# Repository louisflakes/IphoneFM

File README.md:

# IphoneFM

A MagSafe accessory for the iPhone 17 Pro that transmits and receives FM (88–108 MHz).
The board lies flat on the back of the phone and connects to the phone through a very short, flexible USB-C cable.
The iPhone sees a USB audio device: it sends audio to transmit, or plays audio the board receives.
Transmit and receive are half duplex, selected by a TX/RX slider. Three thumbwheels set the frequency; a DIP switch sets the transmit level.

The project also asks a question: can Claude design a working PCB, from requirements to a board JLCPCB assembles in full?

## Status

**Rev A** is the active design: the analog-FM rendition, option D2. The MCU computes the FM modulation and streams it over I²S to a TI LMX2571 synthesizer, whose internal VCO is the carrier ([modulation-strategies.md](design/rev-a/modulation-strategies.md)). Every part is checked against its datasheet, every pin is mapped to a net, and the placement is agreed. Next: the KiCad build, following [kicad-build-procedure.md](design/rev-a/kicad-build-procedure.md) one step at a time.

| Design | Transmitter | Status |
|---|---|---|
| Rev A (analog FM, D2) | TI LMX2571, direct digital FM | **Active** |
| Plan C | onsemi LV2285VB | Archived: the transmitter is obsolete and needs a large minimum order |
| Plans A, B | | Archived |

## Rev A design files (`design/rev-a/`)

| File | What it is |
|---|---|
| [netlist.json](design/rev-a/netlist.json) | **Source of truth:** every part (designator, part number, JLC code, package) and every pin with its net |
| [bom.md](design/rev-a/bom.md) | Why each part and value was chosen, chain by chain, with datasheet pages |
| [wiring.html](design/rev-a/wiring.html) | Wiring diagram and netlist table |
| [layout.html](design/rev-a/layout.html) | True-size parts on the board envelope, and the Rev A placement |
| [placement-rules.md](design/rev-a/placement-rules.md) | Placement rules, with the user's feedback |
| [sourcing.md](design/rev-a/sourcing.md) | Key parts, JLC stock and second routes |
| [modulation-strategies.md](design/rev-a/modulation-strategies.md) | Why direct digital FM on the LMX2571 |
| [verification.md](design/rev-a/verification.md) | The checks that keep every file, and later KiCad, in step |
| [kicad-build-procedure.md](design/rev-a/kicad-build-procedure.md) | The KiCad build, one reviewed step at a time |

The KiCad project goes in `kicad/rev-a/`. Open the `.html` pages in a browser; `layout.html` needs `local/apple/phone-outline.js`, which stays on the design PC (Apple's drawings say not to republish it).

## Checks

```
python tools/netcheck.py                      # netlist.json against itself, bom.md and wiring.html
python tools/kicadcheck.py --net … --pcb …    # KiCad's exports against netlist.json and the Rev A placement
python tools/kicadcheck_test.py               # proves kicadcheck catches real faults
```

## Open items

1. KiCad build: [kicad-build-procedure.md](design/rev-a/kicad-build-procedure.md).
2. Before ordering: re-run JLC stock for the thin parts (Si4705, LMX2571) and the two global-sourcing parts (STM32U535, TDP06 DIP).
3. Bench checks on the first boards: which slider direction is TX (TP4); the SMA's centre contact; transmit level and harmonics in the Faraday cage against FCC §15.239 as a target; the receiver's matching inductor L1 by RSSI sweep (AN383 p50–53); 3V3 current.
4. Firmware: UAC2 audio, FM stereo multiplex and pre-emphasis, the I²S deviation stream to the LMX2571, receiver control over I²C, wheels, DIP-aware power setting, LED.
5. MagSafe enclosure (user-owned), with slots for the wheels, slider, DIP levers and USB-C, and a light pipe for the LED.

## Repository layout

| Path | Contents |
|---|---|
| `design/rev-a/` | The active design (above) |
| `kicad/rev-a/` | The KiCad project |
| `design/archive/` | Plans A, B and C, no longer developed |
| `docs/decisions.md` | Design decisions and their sources |
| `docs/pcb-design-workflow.md` | PCB capture and layout workflow and rules, cited to reference books, with conflicts flagged |
| `docs/reference-designs.md` | Existing FM transmitter designs, for patterns only |
| `docs/datasheets/` | Every datasheet and spec the design was checked against, with an index |
| `tools/` | Design checks, DigiKey/JLC stock scripts, KiCad setup |
| `.mcp.json` | KiCad MCP server for Claude Code |
| `Imported/` | Notes from an earlier session, kept for later reference |

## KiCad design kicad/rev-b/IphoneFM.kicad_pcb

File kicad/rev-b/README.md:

KiCad project for IphoneFM Rev B: Rev A (tag rev-a-reviewed) with the new front panel. Built from ../../design/rev-b/build-procedure.md; checked with ../../tools/kicadcheck.py (IPHONEFM_REV=rev-b).

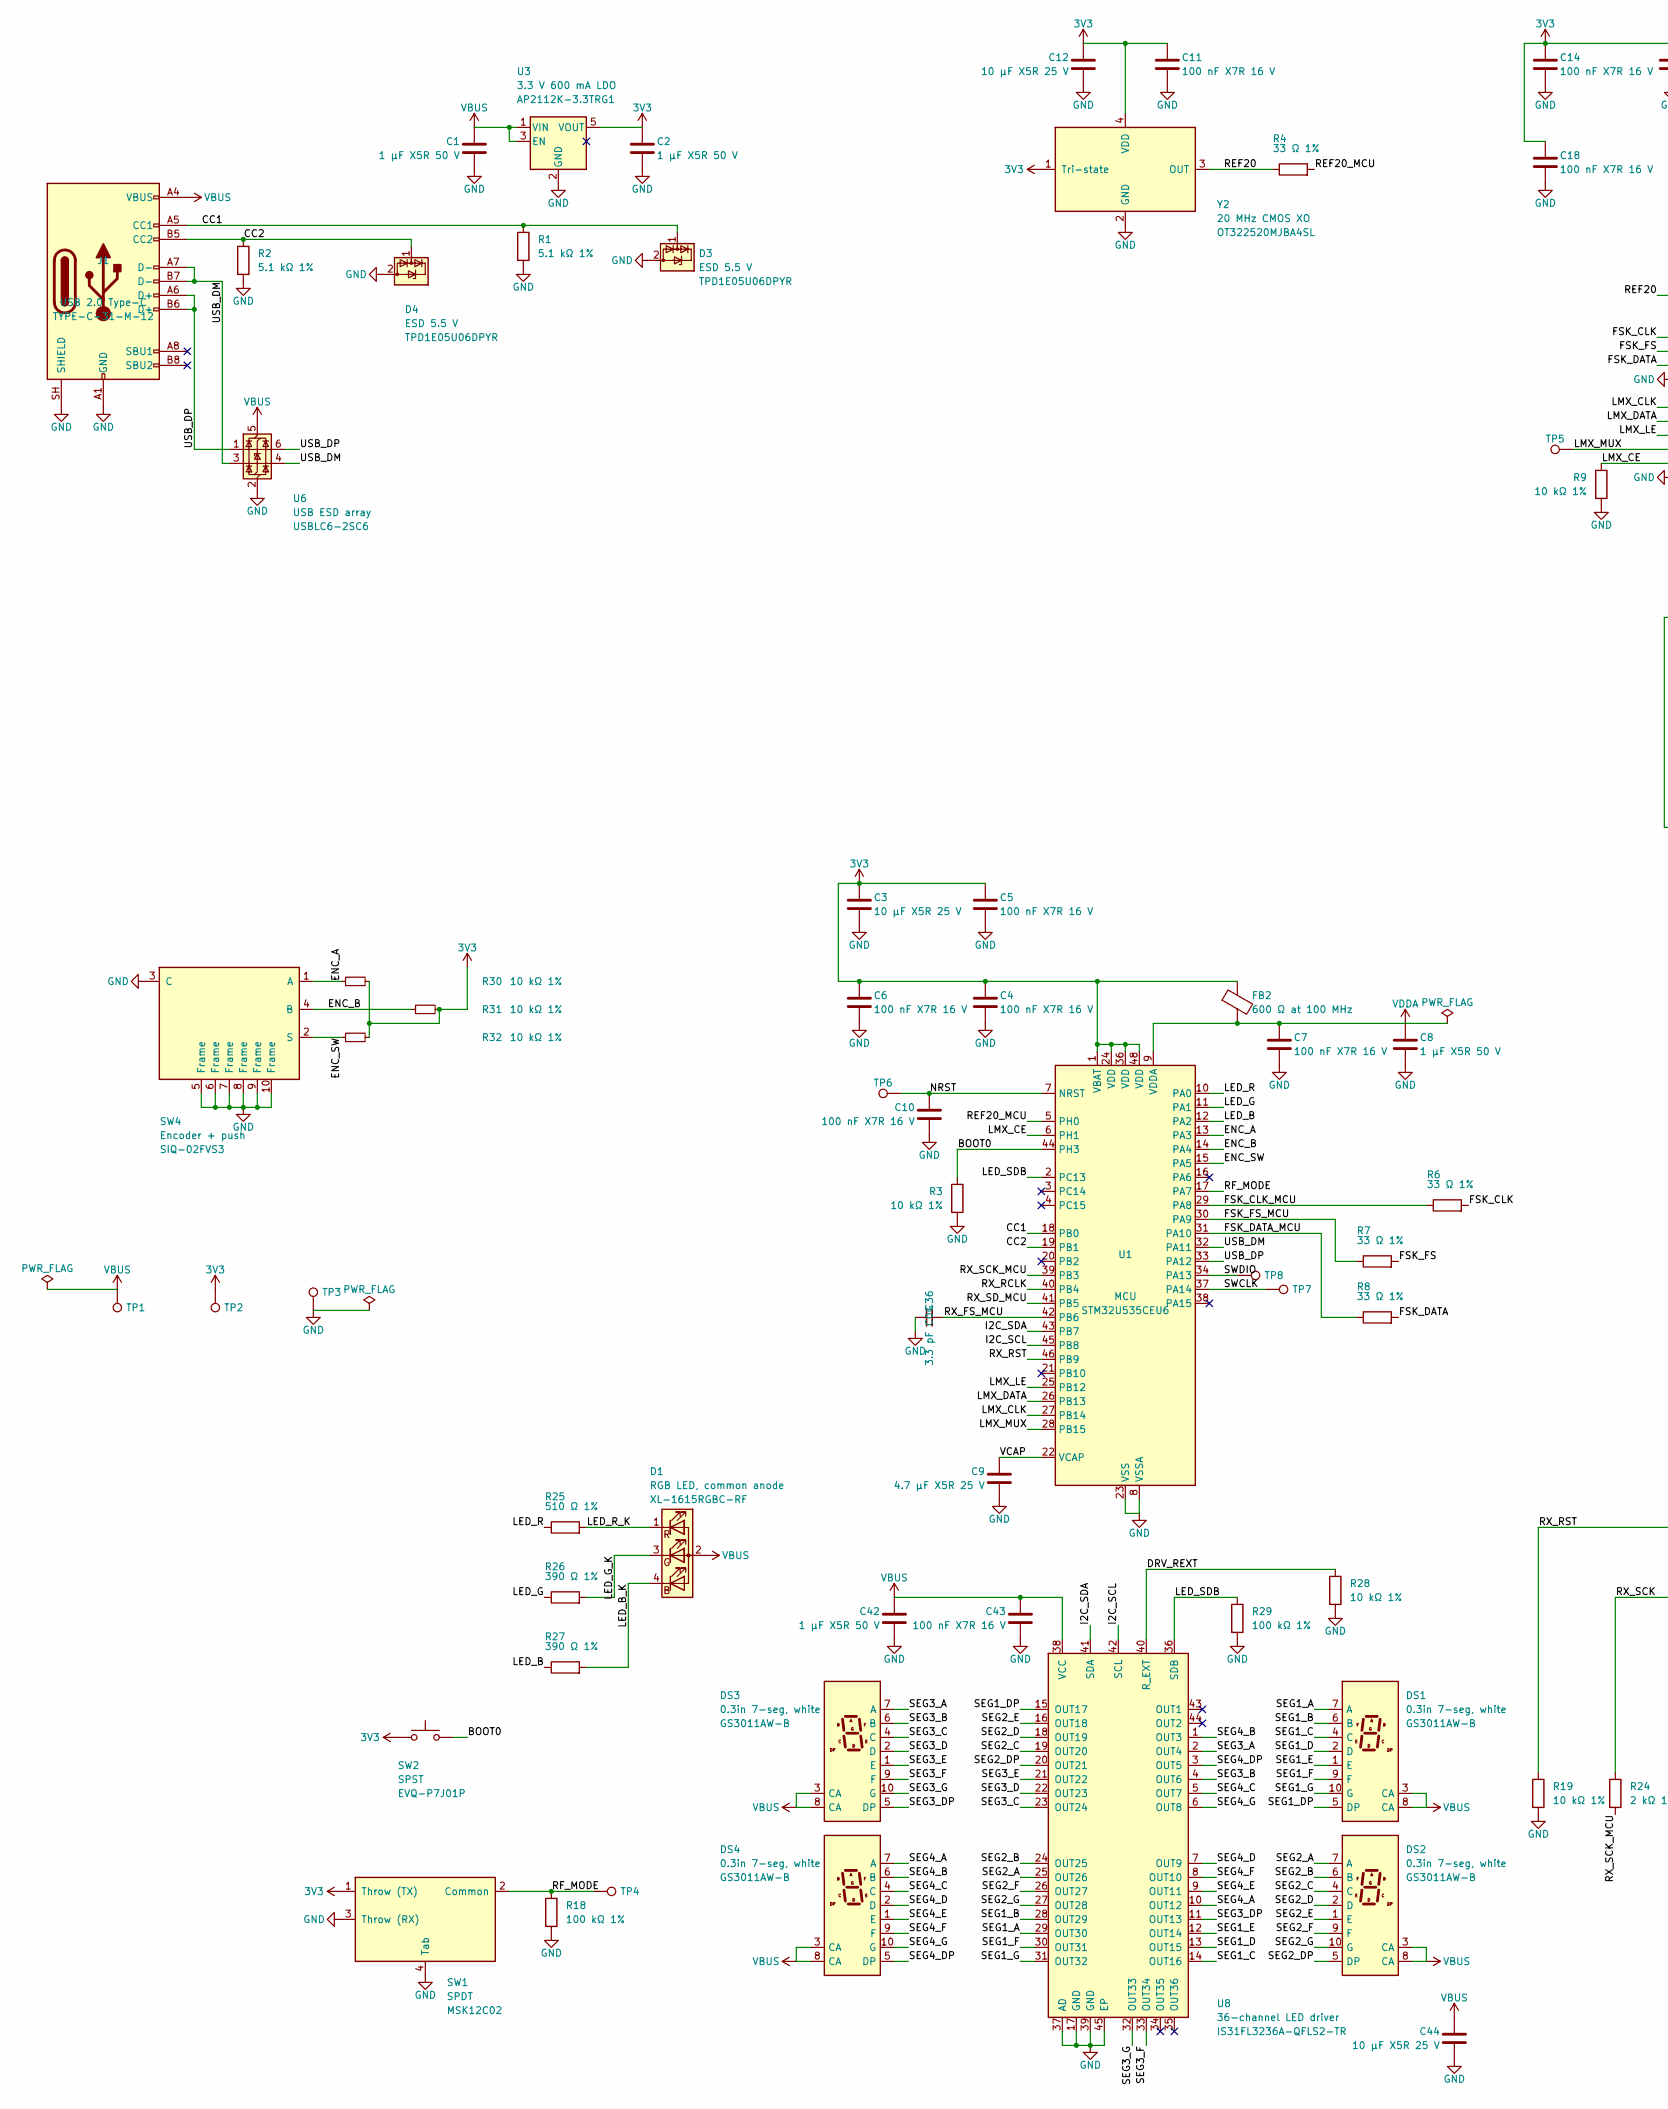
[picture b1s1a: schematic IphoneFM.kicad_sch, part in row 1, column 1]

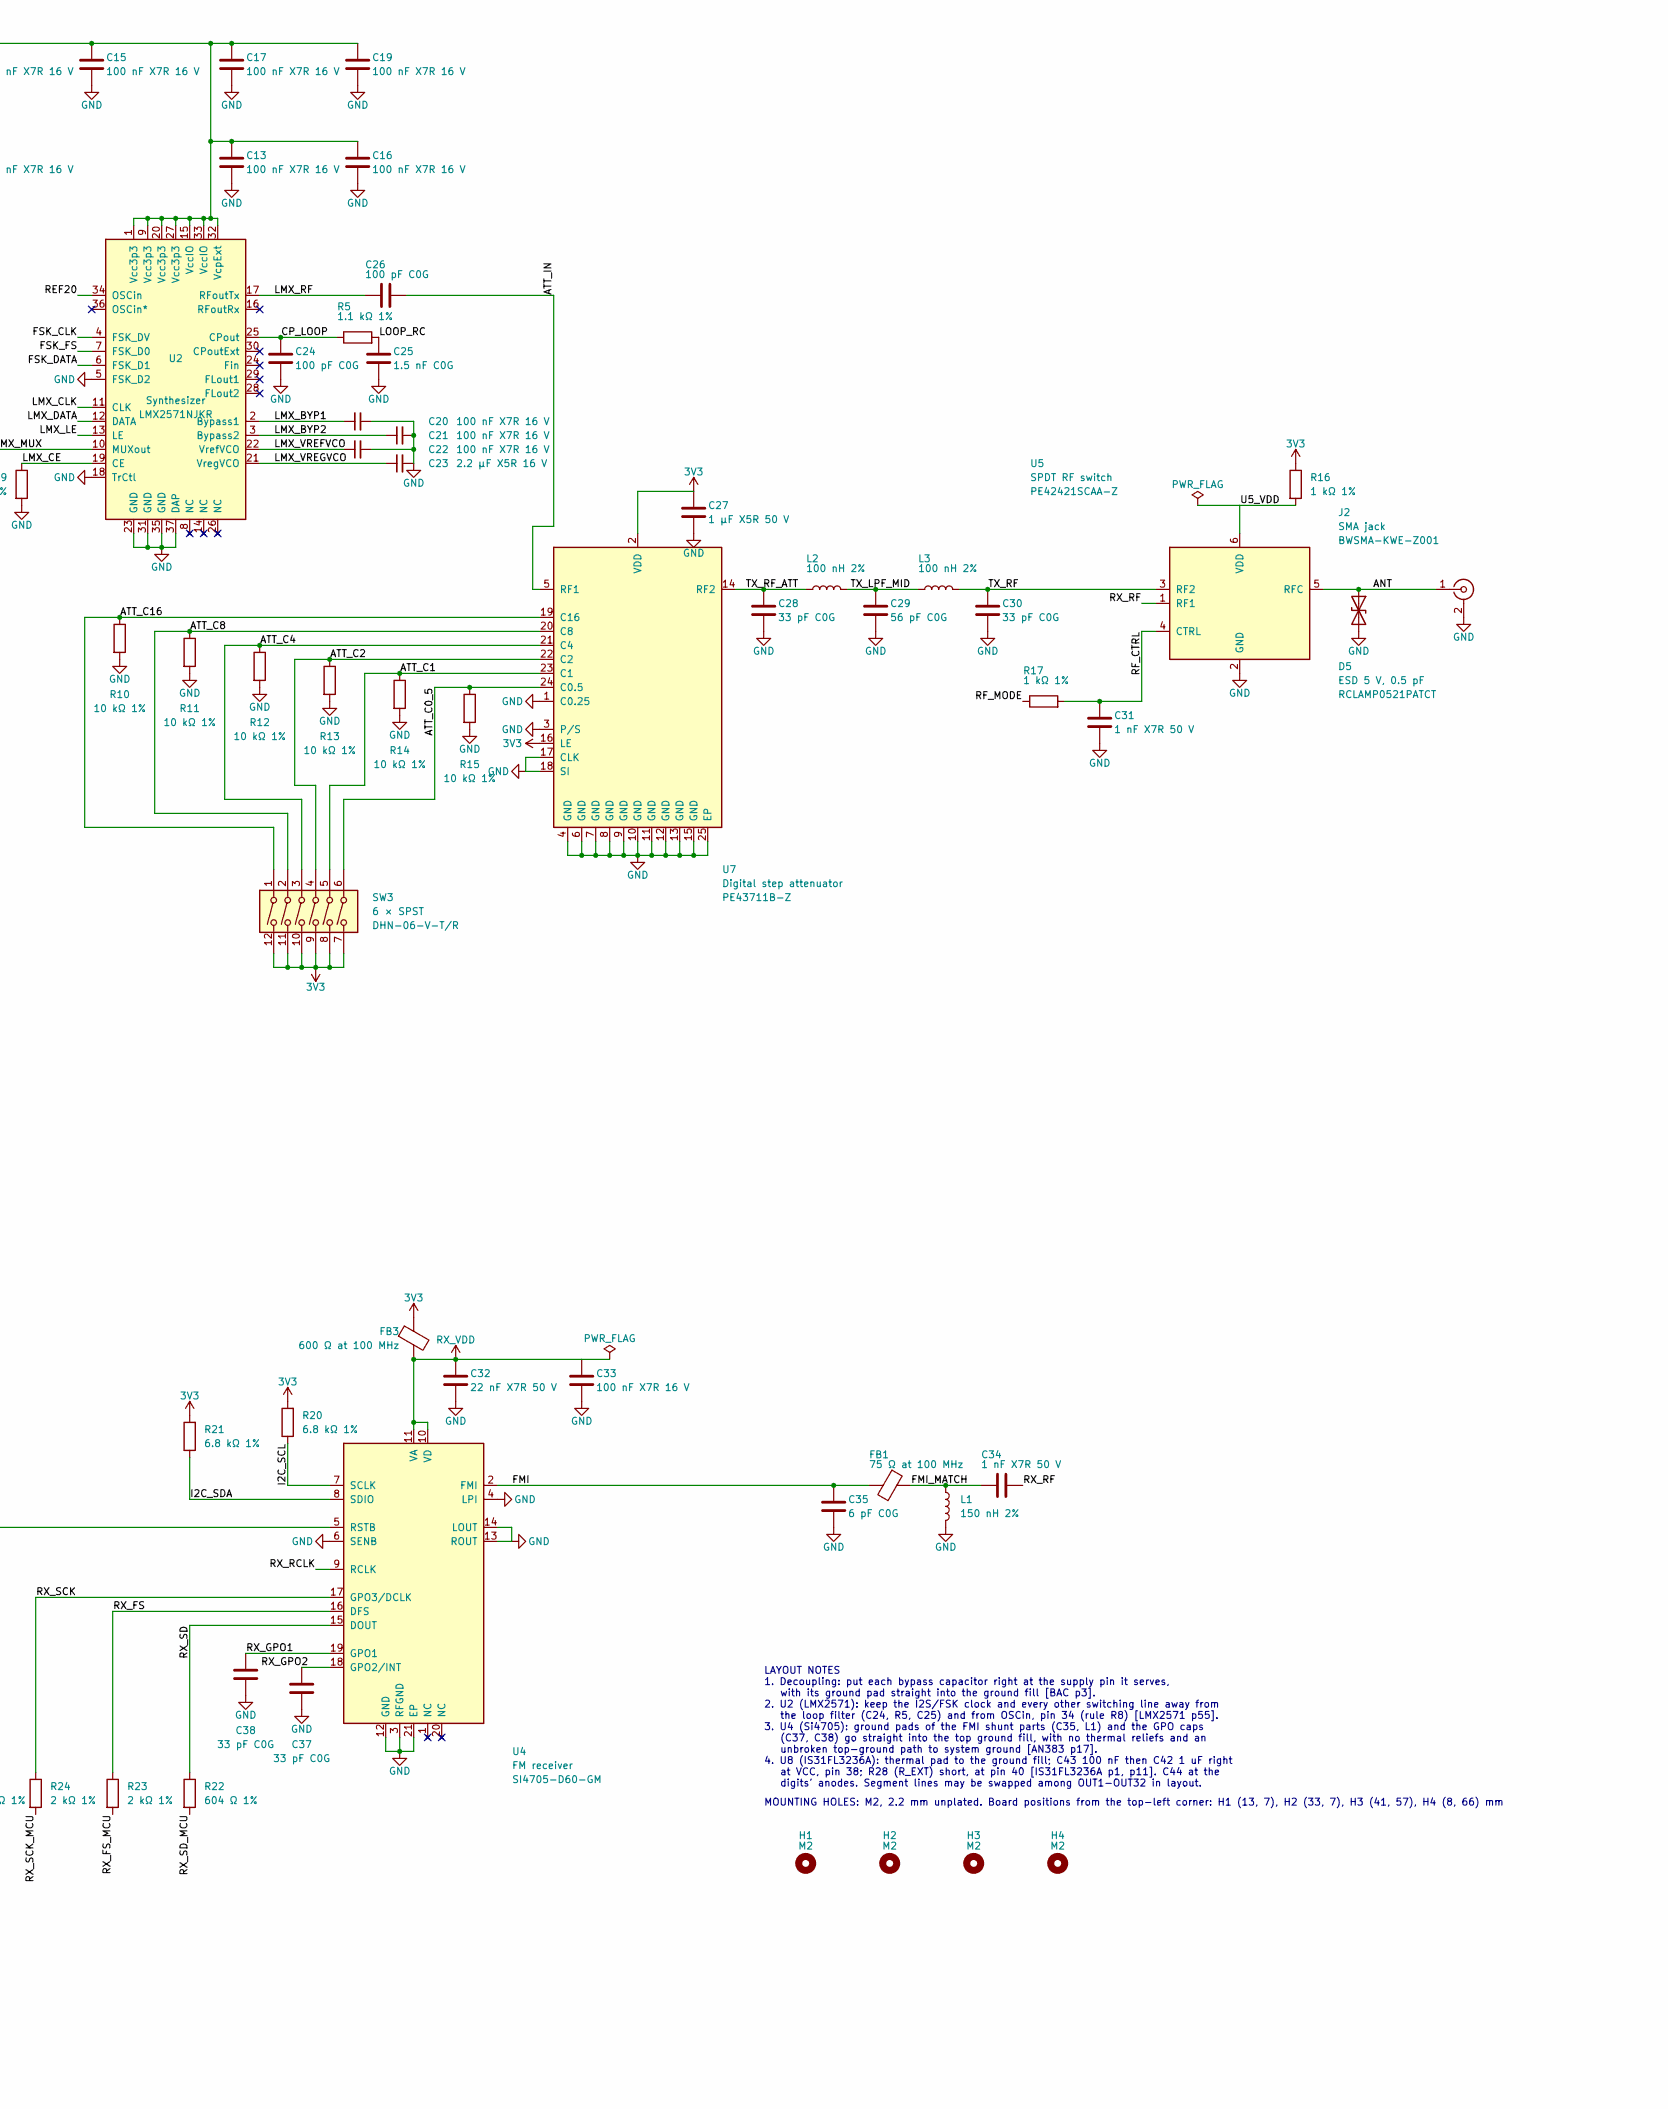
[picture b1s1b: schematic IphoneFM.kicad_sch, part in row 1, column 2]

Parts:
C1, C2, C8, C27, C42: 1 µF X5R 50 V; C_0603_1608Metric; MPN CL10A105KB8NNNC; LCSC C15849
C3, C12, C44: 10 µF X5R 25 V; C_0805_2012Metric; MPN CL21A106KAYNNNE; LCSC C15850
C4, C5, C6, C7, C10, C11, C13, C14, C15, C16, C17, C18, C19, C20, C21, C22, C33, C43: 100 nF X7R 16 V; C_0402_1005Metric; MPN CL05B104KO5NNNC; LCSC C1525
C9: 4.7 µF X5R 25 V; C_0805_2012Metric; MPN CL21A475KAQNNNE; LCSC C1779
C23: 2.2 µF X5R 16 V; C_0603_1608Metric; MPN CL10A225KO8NNNC; LCSC C23630
C24, C26: 100 pF C0G; C_0402_1005Metric; MPN 0402CG101J500NT; LCSC C1546
C25: 1.5 nF C0G; C_0402_1005Metric; MPN GRM1555C1H152JA01D; LCSC C668348
C28, C30, C37, C38: 33 pF C0G; C_0402_1005Metric; MPN 0402CG330J500NT; LCSC C1562
C29: 56 pF C0G; C_0402_1005Metric; MPN CC0402JRNPO9BN560; LCSC C107007
C31, C34: 1 nF X7R 50 V; C_0402_1005Metric; MPN 0402B102K500NT; LCSC C1523
C32: 22 nF X7R 50 V; C_0402_1005Metric; MPN 0402B223K500NT; LCSC C1532
C35: 6 pF C0G; C_0402_1005Metric; MPN GJM1555C1H6R0CB01D; LCSC C161330
C36: 3.3 pF C0G; C_0402_1005Metric; MPN GRM1555C1H3R3CA01D; LCSC C76968
D1: RGB LED, common anode; LED_RGB_XINGLIGHT_XL-1615RGBC_1.6x1.5mm; MPN XL-1615RGBC-RF; LCSC C965840
D3, D4: ESD 5.5 V; Texas_DPY0002A_0.6x1mm_P0.65mm; MPN TPD1E05U06DPYR; LCSC C436349
D5: ESD 5 V, 0.5 pF; D_SOD-882; MPN RCLAMP0521PATCT; LCSC C117554
DS1, DS2, DS3, DS4: 0.3in 7-seg, white; LED_7Segment_Guangcai_GS3011_7.3x12mm_P1.5mm; MPN GS3011AW-B; LCSC C22462661
FB1: 75 Ω at 100 MHz; L_0402_1005Metric; MPN BLM15GA750SN1D; LCSC C113009
FB2, FB3: 600 Ω at 100 MHz; L_0402_1005Metric; MPN BLM15AG601SN1D; LCSC C76884
H1, H2, H3, H4: M2; MountingHole_2.2mm_M2
J1: USB 2.0 Type-C; USB_C_Receptacle_HRO_TYPE-C-31-M-12_2020; MPN TYPE-C-31-M-12; LCSC C165948
J2: SMA jack; SMA_BAT_Wireless_BWSMA-KWE-Z001; MPN BWSMA-KWE-Z001; LCSC C496551
L1: 150 nH 2%; L_0603_1608Metric; MPN LQW18ANR15G00D; LCSC C113131
L2, L3: 100 nH 2%; L_0603_1608Metric; MPN LQW18ANR10G00D; LCSC C98088
R1, R2: 5.1 kΩ 1%; R_0402_1005Metric; MPN 0402WGF5101TCE; LCSC C25905
R3, R9, R10, R11, R12, R13, R14, R15, R19, R28, R30, R31, R32: 10 kΩ 1%; R_0402_1005Metric; MPN 0402WGF1002TCE; LCSC C25744
R4, R6, R7, R8: 33 Ω 1%; R_0402_1005Metric; MPN 0402WGF330JTCE; LCSC C25105
R5: 1.1 kΩ 1%; R_0402_1005Metric; MPN ERJ-2RKF1101X; LCSC C409028
R16, R17: 1 kΩ 1%; R_0402_1005Metric; MPN 0402WGF1001TCE; LCSC C11702
R18, R29: 100 kΩ 1%; R_0402_1005Metric; MPN 0402WGF1003TCE; LCSC C25741
R20, R21: 6.8 kΩ 1%; R_0402_1005Metric; MPN RC0402FR-076K8L; LCSC C93940
R22: 604 Ω 1%; R_0402_1005Metric; MPN RC0402FR-07604RL; LCSC C273693
R23, R24: 2 kΩ 1%; R_0402_1005Metric; MPN 0402WGF2001TCE; LCSC C4109
R25: 510 Ω 1%; R_0402_1005Metric; MPN 0402WGF5100TCE; LCSC C25123
R26, R27: 390 Ω 1%; R_0402_1005Metric; MPN RC0402FR-07390RL; LCSC C137997
SW1: SPDT; SW_SPDT_Shouhan_MSK12C02_Tabs4; MPN MSK12C02; LCSC C431540
SW2: SPST; SW_SPST_EVQP7A; MPN EVQ-P7J01P; LCSC C2828254
SW3: 6 × SPST; SW_DIP_SPSTx06_Slide_Diptronics_DHN-06_W6.15mm_P1.27mm; MPN DHN-06-V-T/R; LCSC C224997
SW4: Encoder + push; RotaryEncoder_Switch_Mitsumi_SIQ-02FVS3; MPN SIQ-02FVS3; LCSC C2925423
TP1: VBUS; TestPoint_Pad_D1.5mm
TP2: 3V3; TestPoint_Pad_D1.5mm
TP3: GND; TestPoint_Pad_D1.5mm
TP4: RF_MODE; TestPoint_Pad_D1.5mm
TP5: LMX_MUX; TestPoint_Pad_D1.5mm
TP6: NRST; TestPoint_Pad_D1.5mm
TP7: SWCLK; TestPoint_Pad_D1.5mm
TP8: SWDIO; TestPoint_Pad_D1.5mm
U1: MCU; QFN-48-1EP_7x7mm_P0.5mm_EP5.6x5.6mm; MPN STM32U535CEU6; LCSC C22454224
U2: Synthesizer; TI_NJK0036A_WQFN-36-1EP_6x6mm_P0.5mm_EP4.6x4.6mm; MPN LMX2571NJKR; LCSC C440388
U3: 3.3 V 600 mA LDO; SOT-23-5; MPN AP2112K-3.3TRG1; LCSC C51118
U4: FM receiver; SiliconLabs_QFN-20-1EP_3x3mm_P0.5mm_EP1.8x1.8mm; MPN SI4705-D60-GM; LCSC C1526114
U5: SPDT RF switch; SOT-363_SC-70-6; MPN PE42421SCAA-Z; LCSC C470893
U6: USB ESD array; SOT-23-6; MPN USBLC6-2SC6; LCSC C7519
U7: Digital step attenuator; QFN-24-1EP_4x4mm_P0.5mm_EP2.75x2.75mm; MPN PE43711B-Z; LCSC C470929
U8: 36-channel LED driver; Lumissil_QFN-44-1EP_5x5mm_P0.4mm_EP2.45x2.45mm; MPN IS31FL3236A-QFLS2-TR; LCSC C246443
Y2: 20 MHz CMOS XO; Oscillator_SMD_SiT_PQFN-4Pin_3.2x2.5mm; MPN OT322520MJBA4SL; LCSC C725987

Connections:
3V3: C2.1, C3.1, C4.1, C5.1, C6.1, C11.1, C12.1, C13.1, C14.1, C15.1, C16.1, C17.1, C18.1, C19.1, C27.1, FB2.1, FB3.1, R16.1, R20.2, R21.2, R30.2, R31.2, R32.2, SW1.1 (Throw_(TX)), SW2.1, SW3.7, SW3.8, SW3.9, SW3.10, SW3.11, SW3.12, TP2.1 (1_1), U1.1 (VBAT), U1.24 (VDD), U1.36 (VDD), U1.48 (VDD), U2.1 (Vcc3p3), U2.9 (Vcc3p3), U2.15 (VccIO), U2.20 (Vcc3p3), U2.27 (Vcc3p3), U2.32 (VcpExt), U2.33 (VccIO), U3.5 (VOUT), U7.2 (VDD), U7.16 (LE), Y2.1 (Tri-state), Y2.4 (VDD)
/ANT: D5.1 (A1), J2.1 (In), U5.5 (RFC)
/ATT_C0_5: R15.1, SW3.6, U7.24 (C0.5)
/ATT_C1: R14.1, SW3.5, U7.23 (C1)
/ATT_C2: R13.1, SW3.4, U7.22 (C2)
/ATT_C4: R12.1, SW3.3, U7.21 (C4)
/ATT_C8: R11.1, SW3.2, U7.20 (C8)
/ATT_C16: R10.1, SW3.1, U7.19 (C16)
/ATT_IN: C26.2, U7.5 (RF1)
/BOOT0: R3.1, SW2.2, U1.44 (PH3)
/CC1: D3.1 (I/O), J1.A5 (CC1), R1.1, U1.18 (PB0)
/CC2: D4.1 (I/O), J1.B5 (CC2), R2.1, U1.19 (PB1)
/CP_LOOP: C24.1, R5.1, U2.25 (CPout)
/DRV_REXT: R28.1, U8.40 (R_EXT)
/ENC_A: R30.1, SW4.1 (A), U1.13 (PA3)
/ENC_B: R31.1, SW4.4 (B), U1.14 (PA4)
/ENC_SW: R32.1, SW4.2 (S), U1.15 (PA5)
/FMI: C35.1, FB1.2, U4.2 (FMI)
/FMI_MATCH: C34.2, FB1.1, L1.1
/FSK_CLK: R6.2, U2.4 (FSK_DV)
/FSK_CLK_MCU: R6.1, U1.29 (PA8)
/FSK_DATA: R8.2, U2.6 (FSK_D1)
/FSK_DATA_MCU: R8.1, U1.31 (PA10)
/FSK_FS: R7.2, U2.7 (FSK_D0)
/FSK_FS_MCU: R7.1, U1.30 (PA9)
/I2C_SCL: R20.1, U1.45 (PB8), U4.7 (SCLK), U8.42 (SCL)
/I2C_SDA: R21.1, U1.43 (PB7), U4.8 (SDIO), U8.41 (SDA)
/LED_B: R27.1, U1.12 (PA2)
/LED_B_K: D1.4 (BK), R27.2
/LED_G: R26.1, U1.11 (PA1)
/LED_G_K: D1.3 (GK), R26.2
/LED_R: R25.1, U1.10 (PA0)
/LED_R_K: D1.1 (RK), R25.2
/LED_SDB: R29.1, U1.2 (PC13), U8.36 (SDB)
/LMX_BYP1: C20.1, U2.2 (Bypass1)
/LMX_BYP2: C21.1, U2.3 (Bypass2)
/LMX_CE: R9.1, U1.6 (PH1), U2.19 (CE)
/LMX_CLK: U1.27 (PB14), U2.11 (CLK)
/LMX_DATA: U1.26 (PB13), U2.12 (DATA)
/LMX_LE: U1.25 (PB12), U2.13 (LE)
/LMX_MUX: TP5.1 (1_1), U1.28 (PB15), U2.10 (MUXout)
/LMX_RF: C26.1, U2.17 (RFoutTx)
/LMX_VREFVCO: C22.1, U2.22 (VrefVCO)
/LMX_VREGVCO: C23.1, U2.21 (VregVCO)
/LOOP_RC: C25.1, R5.2
/NRST: C10.1, TP6.1 (1_1), U1.7 (NRST)
/REF20: R4.1, U2.34 (OSCin), Y2.3 (OUT)
/REF20_MCU: R4.2, U1.5 (PH0)
/RF_CTRL: C31.1, R17.2, U5.4 (CTRL)
/RF_MODE: R17.1, R18.1, SW1.2 (Common), TP4.1 (1_1), U1.17 (PA7)
/RX_FS: R23.1, U4.16 (DFS)
/RX_FS_MCU: C36.1, R23.2, U1.42 (PB6)
/RX_GPO1: C38.1, U4.19 (GPO1)
/RX_GPO2: C37.1, U4.18 (GPO2/INT)
/RX_RCLK: U1.40 (PB4), U4.9 (RCLK)
/RX_RF: C34.1, U5.1 (RF1)
/RX_RST: R19.1, U1.46 (PB9), U4.5 (RSTB)
/RX_SCK: R24.1, U4.17 (GPO3/DCLK)
/RX_SCK_MCU: R24.2, U1.39 (PB3)
/RX_SD: R22.1, U4.15 (DOUT)
/RX_SD_MCU: R22.2, U1.41 (PB5)
/SEG1_A: DS1.7 (A), U8.29 (OUT30)
/SEG1_B: DS1.6 (B), U8.28 (OUT29)
/SEG1_C: DS1.4 (C), U8.14 (OUT16)
/SEG1_D: DS1.2 (D), U8.13 (OUT15)
/SEG1_DP: DS1.5 (DP), U8.15 (OUT17)
/SEG1_E: DS1.1 (E), U8.12 (OUT14)
/SEG1_F: DS1.9 (F), U8.30 (OUT31)
/SEG1_G: DS1.10 (G), U8.31 (OUT32)
/SEG2_A: DS2.7 (A), U8.25 (OUT26)
/SEG2_B: DS2.6 (B), U8.24 (OUT25)
/SEG2_C: DS2.4 (C), U8.19 (OUT20)
/SEG2_D: DS2.2 (D), U8.18 (OUT19)
/SEG2_DP: DS2.5 (DP), U8.20 (OUT21)
/SEG2_E: DS2.1 (E), U8.16 (OUT18)
/SEG2_F: DS2.9 (F), U8.26 (OUT27)
/SEG2_G: DS2.10 (G), U8.27 (OUT28)
/SEG3_A: DS3.7 (A), U8.2 (OUT4)
/SEG3_B: DS3.6 (B), U8.4 (OUT6)
/SEG3_C: DS3.4 (C), U8.23 (OUT24)
/SEG3_D: DS3.2 (D), U8.22 (OUT23)
/SEG3_DP: DS3.5 (DP), U8.11 (OUT13)
/SEG3_E: DS3.1 (E), U8.21 (OUT22)
/SEG3_F: DS3.9 (F), U8.33 (OUT34)
/SEG3_G: DS3.10 (G), U8.32 (OUT33)
/SEG4_A: DS4.7 (A), U8.10 (OUT12)
/SEG4_B: DS4.6 (B), U8.1 (OUT3)
/SEG4_C: DS4.4 (C), U8.5 (OUT7)
/SEG4_D: DS4.2 (D), U8.7 (OUT9)
/SEG4_DP: DS4.5 (DP), U8.3 (OUT5)
/SEG4_E: DS4.1 (E), U8.9 (OUT11)
/SEG4_F: DS4.9 (F), U8.8 (OUT10)
/SEG4_G: DS4.10 (G), U8.6 (OUT8)
/SWCLK: TP7.1 (1_1), U1.37 (PA14)
/SWDIO: TP8.1 (1_1), U1.34 (PA13)
/TX_LPF_MID: C29.1, L2.2, L3.1
/TX_RF: C30.1, L3.2, U5.3 (RF2)
/TX_RF_ATT: C28.1, L2.1, U7.14 (RF2)
/U5_VDD: R16.2, U5.6 (VDD)
/USB_DM: J1.A7 (D-), J1.B7 (D-), U1.32 (PA11), U6.3 (I/O2), U6.4 (I/O2)
/USB_DP: J1.A6 (D+), J1.B6 (D+), U1.33 (PA12), U6.1 (I/O1), U6.6 (I/O1)
/VCAP: C9.1, U1.22 (VCAP)
GND: C1.2, C2.2, C3.2, C4.2, C5.2, C6.2, C7.2, C8.2, C9.2, C10.2, C11.2, C12.2, C13.2, C14.2, C15.2, C16.2, C17.2, C18.2, C19.2, C20.2, C21.2, C22.2, C23.2, C24.2, C25.2, C27.2, C28.2, C29.2, C30.2, C31.2, C32.2, C33.2, C35.2, C36.2, C37.2, C38.2, C42.2, C43.2, C44.2, D3.2 (GND), D4.2 (GND), D5.2 (A2), J1.A1 (GND), J1.A12 (GND), J1.B1 (GND), J1.B12 (GND), J1.SH (SHIELD), J2.2 (Ext), L1.2, R1.2, R2.2, R3.2, R9.2, R10.2, R11.2, R12.2, R13.2, R14.2, R15.2, R18.2, R19.2, R28.2, R29.2, SW1.3 (Throw_(RX)), SW1.4 (Tab), SW4.3 (C), SW4.5 (Frame), SW4.6 (Frame), SW4.7 (Frame), SW4.8 (Frame), SW4.9 (Frame), SW4.10 (Frame), TP3.1 (1_1), U1.8 (VSSA), U1.23 (VSS), U1.35 (VSS), U1.47 (VSS), U1.49 (VSS), U2.5 (FSK_D2), U2.18 (TrCtl), U2.23 (GND), U2.31 (GND), U2.35 (GND), U2.37 (DAP), U3.2 (GND), U4.3 (RFGND), U4.4 (LPI), U4.6 (SENB), U4.12 (GND), U4.13 (ROUT), U4.14 (LOUT), U4.21 (EP), U5.2 (GND), U6.2 (GND), U7.1 (C0.25), U7.3 (P/S), U7.4 (GND), U7.6 (GND), U7.7 (GND), U7.8 (GND), U7.9 (GND), U7.10 (GND), U7.11 (GND), U7.12 (GND), U7.13 (GND), U7.15 (GND), U7.17 (CLK), U7.18 (SI), U7.25 (EP), U8.17 (GND), U8.37 (AD), U8.39 (GND), U8.45 (EP), Y2.2 (GND)
RX_VDD: C32.1, C33.1, FB3.2, U4.10 (VD), U4.11 (VA)
VBUS: C1.1, C42.1, C43.1, C44.1, D1.2 (A), DS1.3 (CA), DS1.8 (CA), DS2.3 (CA), DS2.8 (CA), DS3.3 (CA), DS3.8 (CA), DS4.3 (CA), DS4.8 (CA), J1.A4 (VBUS), J1.A9 (VBUS), J1.B4 (VBUS), J1.B9 (VBUS), TP1.1 (1_1), U3.1 (VIN), U3.3 (EN), U6.5 (VBUS), U8.38 (VCC)
VDDA: C7.1, C8.1, FB2.2, U1.9 (VDDA)

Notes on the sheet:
MOUNTING HOLES: M2, 2.2 mm unplated. Board positions from the top-left corner: H1 (13, 7), H2 (33, 7), H3 (41, 57), H4 (8, 66) mm
LAYOUT NOTES 1. Decoupling: put each bypass capacitor right at the supply pin it serves, with its ground pad straight into the ground fill [BAC p3]. 2. U2 (LMX2571): keep the I2S/FSK clock and every other switching line away from the loop filter (C24, R5, C25) and from OSCin, pin 34 (rule R8) [LMX2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

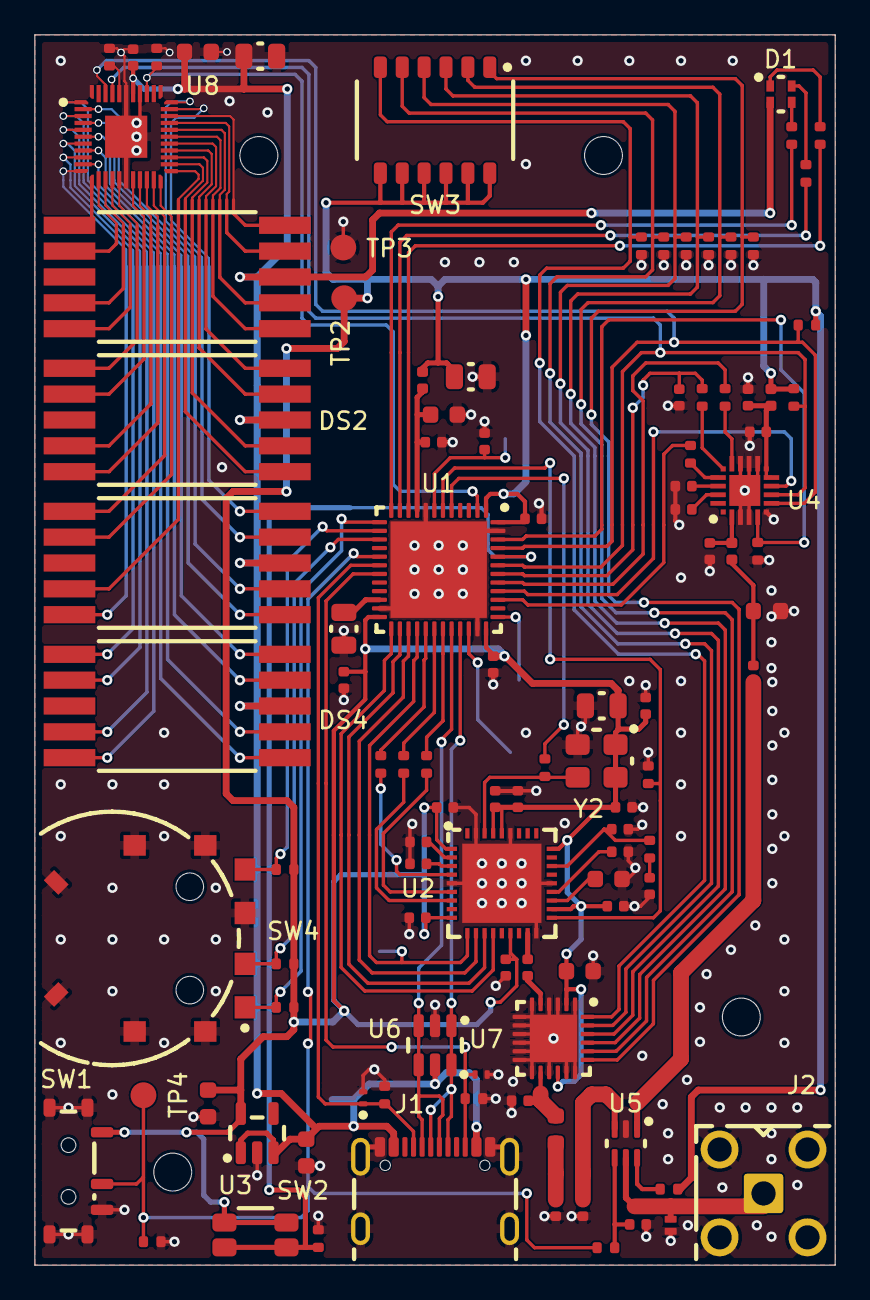
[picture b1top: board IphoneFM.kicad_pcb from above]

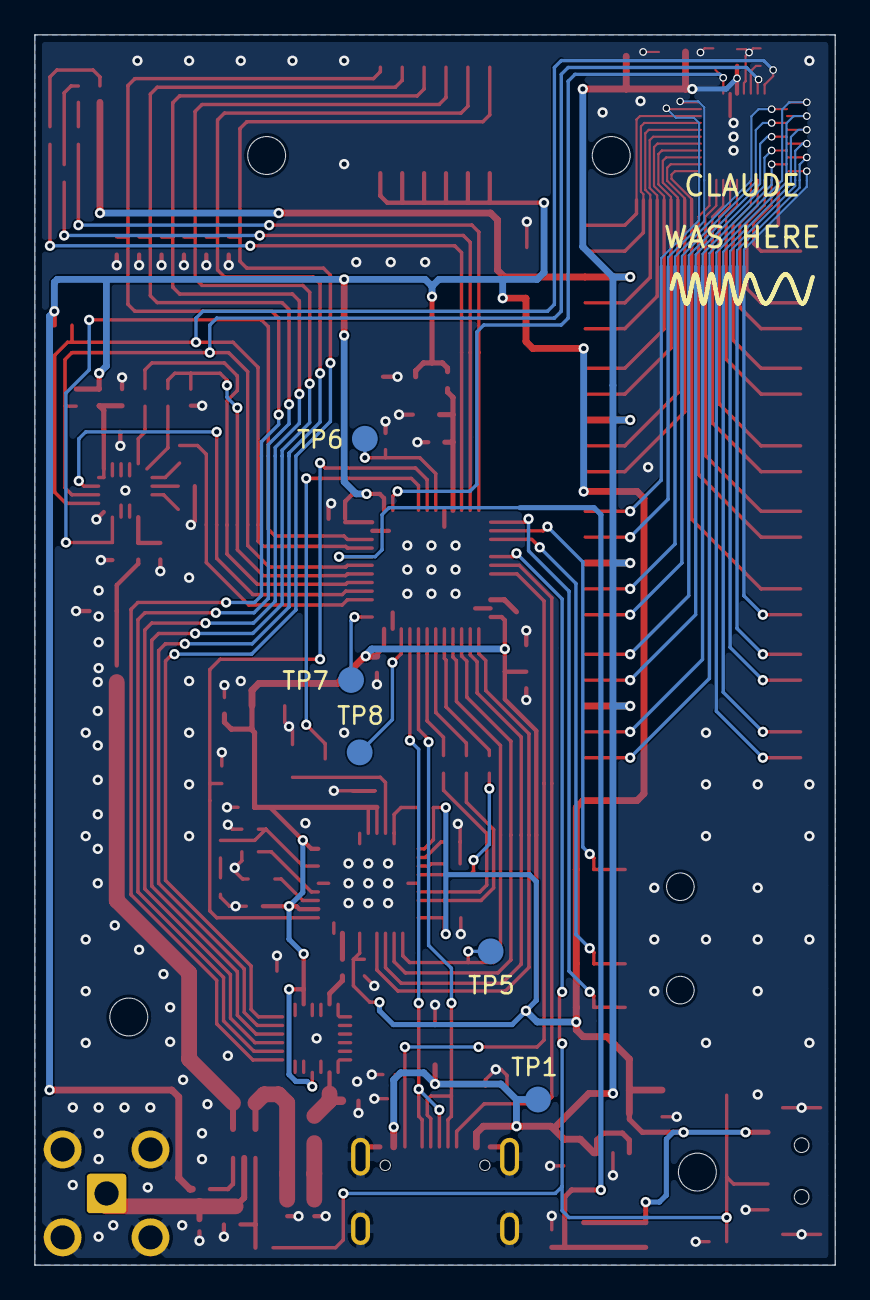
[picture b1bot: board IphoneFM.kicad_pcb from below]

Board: 2 copper layers, 46.5 x 71.4 mm, 114 parts (5 on the bottom side), 106 nets.

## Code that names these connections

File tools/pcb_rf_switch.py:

"""Step 4.9: places U5 (RF switch), the transmit low-pass filter FL1 and the parts at U5's pins, live in the board open in
KiCad (one undo step). U5's pins run receive (1), transmit (3), antenna (5) round the chip, so with the antenna to the
right (J2), the transmit line comes down the left and the receive line leaves upward to U4 above (the user's choice,
2026-10-23: no RF lines cross). The filter is an L just west of U5, its two inductors at 90 degrees (AN4169 p11-12):
C28 shunt -> L2 (vertical) -> C29 shunt -> L3 (horizontal) -> C30 shunt -> U5 pin 3. Every courtyard keeps the 0.35 mm
gap pcb_local.py uses. Positions are worked out from the courtyards below, not read off a drawing.
Usage (from the repository root, board open in KiCad): python tools/pcb_rf_switch.py [--dry-run]"""
import sys

GAP = 0.35
U5 = (47.0, 125.0)  # the sketch's place; SOT-363 courtyard +-1.45 x +-1.1
PIN3_Y = U5[1] + 0.65  # transmit pin, left side, lower
L06_HX, L06_HY = 1.48, 0.73  # 0603 inductor courtyard half sizes (lying along x)
C04_HX, C04_HY = 0.91, 0.46  # 0402 capacitor
R04_HX, R04_HY = 0.93, 0.47
L06_PAD = 0.7875  # 0603 pad centre from the part centre

u5_left, u5_top, u5_bot, u5_right = U5[0] - 1.45, U5[1] - 1.1, U5[1] + 1.1, U5[0] + 1.45
l3 = (u5_left - GAP - L06_HX, PIN3_Y)                       # L3 lying along the line into pin 3
node2_x, node3_x = l3[0] - L06_PAD, l3[0] + L06_PAD         # its pads: filter middle (left) and TX_RF (right)
below = l3[1] + L06_HY + GAP + C04_HX                       # shunt capacitors standing below L3, centres
l2 = (node2_x, l3[1] - L06_HY - GAP - L06_HX)               # L2 standing above L3's left pad: 90 deg to L3
node1_y = l2[1] - L06_PAD                                   # its top pad: the filter input
c28 = (node2_x + L06_HY + GAP + C04_HX, node1_y)            # input shunt, lying to the right of L2's top pad
c34 = (c28[0] + C04_HX + GAP + C04_HY, u5_top - GAP - C04_HX)  # RX DC block standing above U5 pin 1, clear of C28
r16 = (c34[0] + C04_HY + GAP + R04_HY, c34[1])              # U5 VDD resistor standing above pin 6
d5 = (U5[0] + 1.45 + GAP + 0.6 + 0.05, U5[1] + 0.6)         # antenna ESD, standing just below the antenna line
c31 = (U5[0] + 0.84, u5_bot + GAP + C04_HX)                 # CTRL filter standing below pin 4
r17 = (c31[0] - C04_HY - GAP - R04_HY, c31[1])              # CTRL series resistor beside it

# ref: (x, y, turn) — turns put each part's pad on the line's net toward the line (KiCad turns counter-clockwise)
PLACE = {
    "U5": (U5[0], U5[1], 0),     # antenna pin 5 faces J2 on the right
    "L3": (l3[0], l3[1], 0),     # pad 1 (filter middle) left, pad 2 (TX_RF) right toward pin 3
    "C30": (node3_x, below, -90),  # pad 1 (TX_RF) up, ground pad down
    "C29": (node2_x, below, -90),  # pad 1 (filter middle) up
    "L2": (l2[0], l2[1], -90),   # pad 1 (from U7) up, pad 2 (filter middle) down
    "C28": (c28[0], c28[1], 0),  # pad 1 (from U7) left, toward L2's top pad
    "C34": (c34[0], c34[1], 90),  # pad 1 (RX_RF) down, toward pin 1; the receive line leaves upward
    "R16": (r16[0], r16[1], -90),  # pad 2 (U5_VDD) down, toward pin 6
    "D5": (d5[0], d5[1], -90),   # pad 1 (ANT) up, under the antenna line
    "C31": (c31[0], c31[1], -90),  # pad 1 (RF_CTRL) up, toward pin 4
    "R17": (r17[0], r17[1], 90),  # pad 2 (RF_CTRL) up
}


def main():
    for ref, (x, y, a) in PLACE.items():
        print(f"{ref:4} ({x:7.3f}, {y:7.3f}) {a:4} deg")
    if "--dry-run" in sys.argv:
        return
    from kipy import KiCad
    from kipy.geometry import Vector2, Angle
    board = KiCad().get_board()
    fps = {fp.reference_field.text.value: fp for fp in board.get_footprints()}
    items = []
    for ref, (x, y, a) in PLACE.items():
        fps[ref].position = Vector2.from_xy(round(x * 1e6), round(y * 1e6))
        fps[ref].orientation = Angle.from_degrees(a)
        items.append(fps[ref])
    c = board.begin_commit()
    board.update_items(items)
    board.push_commit(c, "Step 4.9: U5, the TX filter and U5's parts")
    print(f"{len(items)} parts placed")


if __name__ == "__main__":
    main()
